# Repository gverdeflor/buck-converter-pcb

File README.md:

# buck-converter-pcb
A PCB design for a buck converter. Designed in EAGLE.

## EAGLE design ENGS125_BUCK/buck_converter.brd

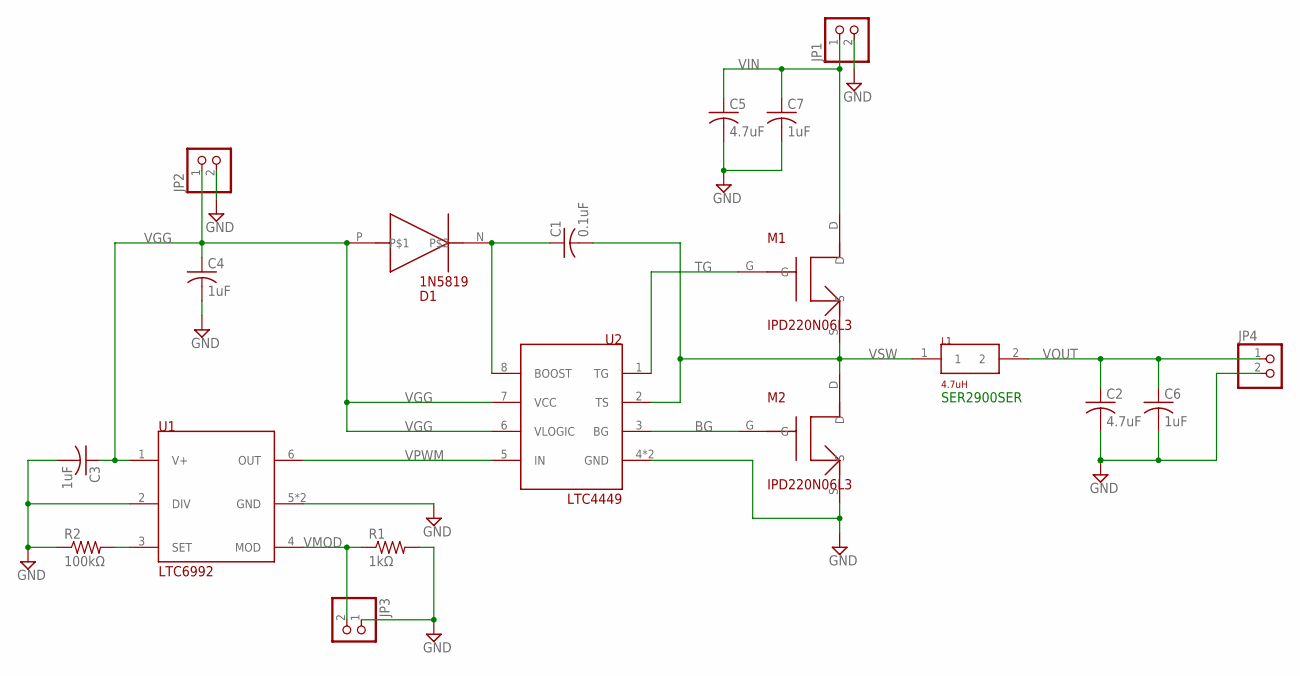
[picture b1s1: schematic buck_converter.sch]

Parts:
C1: 0.1uF; C0805
C2, C5: 4.7uF; C1206
C3, C4, C6, C7: 1uF; C0805
D1: 1N5819; SOD123
JP1, JP2, JP3, JP4: PINHD-1X2; 1X02
L1: 4.7uH; SER2900
M1, M2: IPD220N06L3; DPAK
R1: 1kΩ; R0805
R2: 100kΩ; R0805
U1: LTC6992
U2: LTC4449; DCB8

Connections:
BG: M2.G, U2.3 (BG)
GND: C2.2, C3.2, C4.2, C5.2, C6.2, C7.2, JP1.2, JP2.2, JP3.1, JP4.2, M2.S, R1.2, R2.1, U1.2 (DIV), U1.5 (GND), U1.7 (GND), U2.4 (GND), U2.9 (GND)
unnamed: R2.2, U1.3 (SET)
unnamed: C1.1, D1.N, U2.8 (BOOST)
TG: M1.G, U2.1 (TG)
VGG: C3.1, C4.1, D1.P, JP2.1, U1.1 (V+), U2.6 (VLOGIC), U2.7 (VCC)
VIN: C5.1, C7.1, JP1.1, M1.D
VMOD: JP3.2, R1.1, U1.4 (MOD)
VOUT: C2.1, C6.1, JP4.1, L1.2
VPWM: U1.6 (OUT), U2.5 (IN)
VSW: C1.2, L1.1, M1.S, M2.D, U2.2 (TS)

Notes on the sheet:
SER2900SER

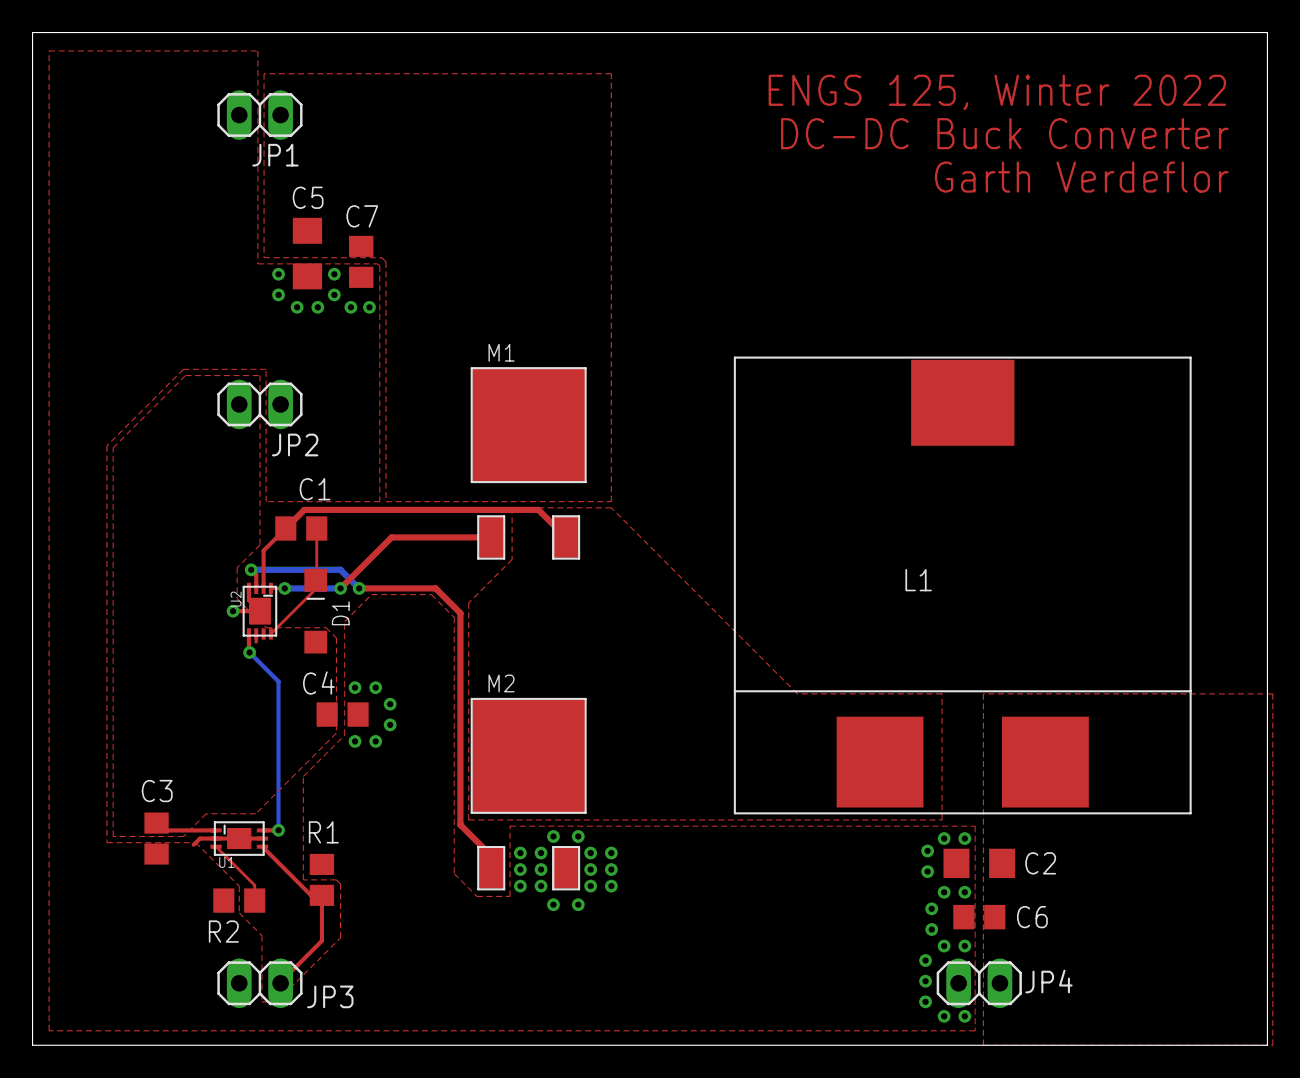
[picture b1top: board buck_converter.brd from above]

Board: 2 copper layers, 75.9 x 62.2 mm, 19 parts (0 on the bottom side), 11 nets.

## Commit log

2022-02-08 Set up project and began schematic capture
2022-02-08 Completed schematic capture from LTSpice circuit
2022-02-08 Removed load resistor and extraneous bypass capacitor in schematic
2022-02-09 Generated board and set DRC rules
2022-02-09 Completed initial component placement
2022-02-09 Defined board shape and added mounting holes to corners
2022-02-09 Added power polygons to top layer
2022-02-09 Added GND plane on bottom layer and completed routing
2022-02-09 Cleaned up polygons and top layer routing
2022-02-09 Removed component values from silkscreen
2022-02-09 Added grounding vias
2022-02-15 Removed mounting holes in corners
2022-02-15 Added silkscreen labels and re-positioned reference designators
2022-02-16 Minor adjustments to polygon borders and trace widths
2022-02-16 Removed wire stub and confirmed DRC check
2022-02-16 Added submission deliverables
